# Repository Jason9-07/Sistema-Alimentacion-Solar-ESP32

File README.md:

# Sistema de Alimentación Solar con ESP32

## Descripción

Este proyecto consiste en el diseño e implementación de un sistema de alimentación basado en energía solar. El sistema utiliza un panel solar para capturar energía del Sol, almacenarla en una batería de litio 18650 y alimentar un microcontrolador ESP32.

El objetivo principal es demostrar el funcionamiento de una fuente de energía renovable aplicada a la electrónica, integrando conocimientos de energías renovables, diseño electrónico y programación.

## Objetivos

* Captar energía solar mediante un panel fotovoltaico.
* Almacenar energía en una batería recargable.
* Alimentar un ESP32 utilizando energía renovable.
* Monitorear el estado del sistema.
* Diseñar una PCB profesional utilizando KiCad.

## Componentes Principales

* ESP32 DevKit V1
* Panel Solar 5V 2W
* TP4056
* Batería 18650
* Pantalla OLED I2C
* AMS1117-3.3
* Resistencias
* Capacitores
* Diodo 1N5819

## Estructura del Proyecto

### Carpeta 3D

Contiene modelos 3D de la caja, soportes y piezas mecánicas.

### Carpeta Hardware

Contiene esquemáticos, diseño PCB, archivos Gerber y hojas de datos.

### Carpeta Software

Contiene el código fuente del ESP32 y las librerías utilizadas.

## Funcionamiento

El panel solar genera energía eléctrica cuando recibe luz solar. El módulo TP4056 controla la carga de la batería 18650. La energía almacenada alimenta al ESP32, que puede mostrar información en una pantalla OLED y controlar distintas funciones del sistema.

## Herramientas Utilizadas

* KiCad
* Arduino IDE
* ESP32
* GitHub

## Autor

Kevin Jason Guzmán Condori

## Licencia

Proyecto educativo desarrollado con fines académicos.

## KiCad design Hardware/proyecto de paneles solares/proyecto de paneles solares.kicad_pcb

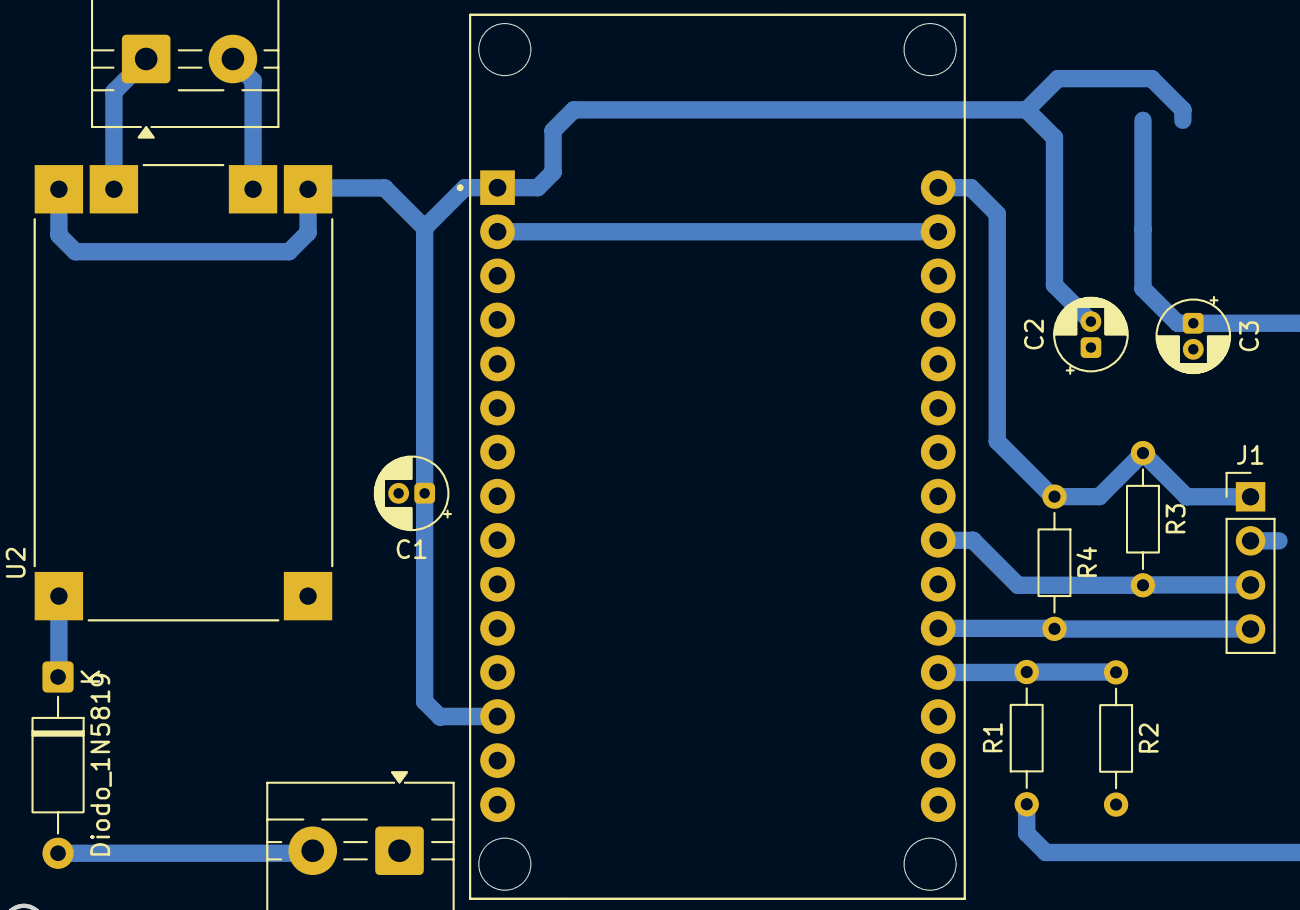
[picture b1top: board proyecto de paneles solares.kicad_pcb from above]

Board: 2 copper layers, 14 parts (1 on the bottom side), 11 nets.

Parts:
C1: 100uF; CP_Radial_D4.0mm_P1.50mm
C2, C3: 10uF; CP_Radial_D4.0mm_P1.50mm
Diodo_1N5819: D_A-405_P10.16mm_Horizontal
J1: Conn_01x04; PinHeader_1x04_P2.54mm_Vertical
J3, J4: Screw_Terminal_01x02; TerminalBlock_MaiXu_MX126-5.0-02P_1x02_P5.00mm
R1, R2: 100k; R_Axial_DIN0204_L3.6mm_D1.6mm_P7.62mm_Horizontal
R3, R4: 4.7k; R_Axial_DIN0204_L3.6mm_D1.6mm_P7.62mm_Horizontal
U1: ESP32-DEVKIT-V1; MODULE_ESP32_DEVKIT_V1
U2: TP4056_MICRO-USB_CHARGER_-_1A; MODULE_TP4056_MICRO-USB_CHARGER_-_1A
U3: AMS1117-3.3; SOT-223-3_TabPin2

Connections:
3.3 V: C3.1, R1.1, U3.2 (VO)
EN: J1.1, R3.1, R4.1, U1.30 (VIN)
GND: C1.2, C2.2, C3.2, J1.2, J3.1, R2.2, U1.2 (GND), U1.29 (GND), U2.IN_N (IN-), U3.1 (GND)
GPIO 34: R1.2, R2.1, U1.19 (D34)
unnamed: Diodo_1N5819.2 (A), J3.2
unnamed: Diodo_1N5819.1 (K), U2.IN_P (IN+)
unnamed: J1.3, R3.2, U1.22 (D33)
unnamed: J1.4, R4.2, U1.20 (D35)
unnamed: J4.1, U2.BAT_P (BAT+)
unnamed: J4.2, U2.BAT_N (BAT-)
unnamed: C1.1, C2.1, U1.1 (3V3), U1.13 (TX0), U2.OUT_N (OUT-), U2.OUT_P (OUT+), U3.3 (VI)

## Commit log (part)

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2026-06-11 Create 3D
2026-06-11 Create IMAGENES
2026-06-29 Create kicad
2026-06-29 Create codigo
